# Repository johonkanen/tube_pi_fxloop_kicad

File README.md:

# Board renders

Rendered by CI from `johonkanen/tube_pi_fxloop_kicad` commit [`0b77b446ac`](https://github.com/johonkanen/tube_pi_fxloop_kicad/commit/0b77b446ac5b79dcb2dc1872e636383eb3f512de) on 2026-11-24 21:37 UTC with 10.0.7.
This branch is force-pushed on every render; do not commit to it.

## tube_pi_fxloop_revb (`rev_b/kicad/tube_pi_fxloop_revb.kicad_pcb`)

Copper layers:
- [B_Cu](tube_pi_fxloop_revb/B_Cu.png)
- [F_Cu](tube_pi_fxloop_revb/F_Cu.png)
- [In1_Cu](tube_pi_fxloop_revb/In1_Cu.png)
- [In2_Cu](tube_pi_fxloop_revb/In2_Cu.png)

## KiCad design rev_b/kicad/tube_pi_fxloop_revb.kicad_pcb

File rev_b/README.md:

# PI + FX loop rev B: schematic and layout (first pass)

The next PI + FX loop board of the 3-channel all-tube head, designed from the simulations and
documents of [tube_amplifier_kicad](https://github.com/johonkanen/tube_amplifier_kicad):
`sim/pi_nfb` (the reference for the PI and the feedback), `sim/fx_loop`, `docs/preamp_regulator.md`
and the interface contract `docs/interfaces.md` (**IF-1.2**: W23 per section 10.1 of 2026-11-22).
Second pass 2026-11-23: what changed and why, the interface check against IF-1.2 and the open items
are in [STATUS.md](STATUS.md), section "Second pass (2026-11-23)"; the third pass (same day,
the user's decisions: W24 Mini-Fit Jr, PI grid leaks to a fixed reference, 480 V raw, normalled
return) in section "Third pass (2026-11-23)". Rev A (the 2010 board,
converted) at the repo root is not touched; `rev_b/` is its own p2k board root
(`p2k_config.py`, PROJECT `tube_pi_fxloop_revb`), the same pattern as tube_preamp_kicad `rev_b/`.

Status and the interface check: [STATUS.md](STATUS.md). **Layout, first pass (2026-11-24):** STATUS.md
"Layout, first pass"; board `kicad/tube_pi_fxloop_revb.kicad_pcb`, renders `docs/layout_*.png`. The
interface sketch it was built on: STATUS.md "Layout sketch: interfaces", [docs/layout_sketch.png](docs/layout_sketch.png).

## Build

```
python3 rev_b/tools/make_lib.py          # lib/ from KiCad's stock symbol libraries (flattened)
python3 rev_b/tools/make_project.py      # project, root sheet, empty sub-sheets
python3 rev_b/tools/sheets/draw_all.py   # draws the five sheets; writes lib/footprint_map.csv and bom/bom.csv
python3 rev_b/tools/verify.py            # KiCad's netlist == the intended connections
rev_b/../tools/p2k/bin/kicad-cli sch erc rev_b/kicad/tube_pi_fxloop_revb.kicad_sch
```

The sheets are generated: edit `tools/sheets/draw_all.py`, not the `.kicad_sch` files, until the
draft is frozen. Drawing style is netlist-first (parts on a grid, a stub and a label on every pin),
exact for ERC and the netlist; a tidy layout pass comes later. **ERC: 0 errors, 0 warnings**
(KiCad 10). `verify.py`: 168 intended nets, 0 mismatches. **252 parts**: 140 R, 54 C, 21
transistors / JFETs, 9 diodes, 8 relays, 7 ICs, 11 connectors, 2 tubes.

**Footprints: all 252 assigned** (`lib/footprint_map.csv`, generated by `draw_all.py`, read by p2k's
sch_builder): KiCad 10 stock libraries except the three power-tab connectors J501-J503, which use
clearly marked local placeholders (`lib/tube_pi_fxloop_revb.pretty/PLACEHOLDER_Tab_x2_*`, two tabs
with 2 legs on 5.00 mm / 1.4 mm drill per interfaces.md 4.1; no stock Faston footprint exists).
Package rules: 0603 logic and gate drive, 0805 low-voltage audio, 1206 at HV nodes or > 0.1 W,
2512 for plate loads and every resistor string across HV (no SMD resistor over 200 V), C0G for
audio caps, THT film where an audio cap sees DC over 50 V, 105 °C electrolytics. The noval sockets
use `Valve:Valve_Noval_P` for now; rev A's `Valve_Noval_Belton_PCD21.00mm` matches the chassis holes
and goes in at layout. **BOM:** `bom/bom.csv`, 89 lines (qty, refs, value, footprint, candidate MPN,
LCSC, DNP, note); 37 lines carry the LCSC number the preamp rev B BOM checked on 2026-11-22 (same
part), the others an MPN or a specification. No stock check run.

| Sheet | Contents |
|---|---|
| 01 | J101 PRE IN (W22-b); 2.2M + 100n into the send cathode follower (V1 pins 1-3), whose grid is the >= 1 Mohm input buffer; SEND_SRC (1k) and the dry divider 47k / 4.7k; J102 FX ribbon (W23-a, IF-1.2: 2 SEND_SRC, 8 PAD_A, 10 PAD_B = GND, 16 RETURN_SIG); RETURN_SIG bleed 2.2M; return input 220n + 100k, the 0 / -20 dB pad (11k shunt switched by a JFET from the rear switch on PAD_A); series-shunt JFET mixer (100k branches, 220k); return stage (V1 pins 6-8, 680R unbypassed); 470n to the attenuator |
| 02 | PI-4 attenuator: five L-sections (1, 2, 4, 8, 16 dB, Z0 49.9k) on G6K-2F-Y relays, energised = section in (NO contacts; unpowered = 0 dB); PI: 10n input, 12AX7 LTP (V2), DN2540 CCS tail with a selected source resistor, equal 100k plates, 22n second-grid cap to the feedback node; J201 DRIVE (W24-a) with the soft-tied ground |
| 03 | J301 FB (W25-b), FB_RTN 0R to AGND (the OT secondary's one reference); per channel: relay at the 8 ohm end (both poles in parallel on the NO contacts), 1M bleed, Rf 100k + Cf 22p, Cres 22n, presence 1k and 22n, the 10-pin pot ribbon J302-J304 (W30-W32-b), NJFET T-switch (series, series, shunt) to the common node; Rbot 4.7k and a DNP step network on the common node |
| 04 | J401 CONTROL (W13-b, template); MCP23S17 (map of interfaces.md 7.2); 2x 74LVC1G11 (branch enable = FX_x AND FX_UNMUTE AND MUTE_ALL_N); 3x DG412 (10 of 12 switches: series gates pulled to -15 V and switched to GND, shunt gates pulled to GND and switched to -15 V); ULN2803A for the 8 relays; DGND island (GNDD) and its soft tie |
| 05 | J501 RAW HV (W03-b, no fuse in the feed); B+PI (3x 130 V, about 388 V) and B+FX (150 + 180 V, about 328 V) regulators, preamp_regulator.md rev B reference (STD4N80K5 DPAK, MMBTA42 on its pour = thermal foldback, HV strings in 2512: Rf 3x 330k, R3 3x 270k, bleed 3x 150k); RC decoupling (2.2k / 22u PI; 10k / 22u per FX triode); heater tabs J502 in (W07-b), J503 out (W08-a), floating; tube heaters |

## Layout (scripted; KiCad 10, KiCadRoutingTools in ~/dev/KiCadRoutingTools)

```
tools/p2k/bin/kipy rev_b/tools/make_pcb.py --force   # board from the netlist: outline / holes / sockets (rev A), connectors, rules
rev_b/layout/place.sh                                 # committed placement (placement_snapshot.json) + fix_place.py; ANNEAL=1 / SEEDS=1,2,.. re-anneals
rev_b/layout/route_chain.sh 0 13                      # heater, pours, 13 routing steps -> rev_b/layout/build/routed.kicad_pcb (about 25 min)
cp rev_b/layout/build/routed.kicad_pcb rev_b/kicad/tube_pi_fxloop_revb.kicad_pcb
tools/p2k/bin/kipy rev_b/layout/drc_exclusions.py      # the 4 explained exclusions (STATUS L3) into the .kicad_pro
rev_b/layout/drc.sh rev_b/kicad/tube_pi_fxloop_revb.kicad_pcb   # DRC + schematic parity with the project rules
tools/p2k/bin/kipy rev_b/layout/mech_check.py rev_b/kicad/tube_pi_fxloop_revb.kicad_pcb
tools/p2k/bin/kipy rev_b/layout/coupling_check.py rev_b/kicad/tube_pi_fxloop_revb.kicad_pcb
rev_b/layout/docs_renders.sh rev_b/kicad/tube_pi_fxloop_revb.kicad_pcb
```

`layout/placement.py` holds every mechanical figure (chassis frame, connector pin-1 positions,
pinned parts, pours); `layout/netclasses.py` the net classes and routing groups; `layout/make_groups.py`
the placement groups, zones and keep-outs; `layout/sketch_*.py` the interface sketch.

## Simulations (rev_b/sim, copies of the master repo's sim folders with the rev B changes)

- `sim/pi_nfb/run_open_load.py` → `results/open_load.md`: the PI loop margins with the rev B caps,
  the CCS tail and equal plates, with the speaker, an 8 ohm resistor, **no load** and a 100 ohm
  safety load. Result: loaded margins are as pi_nfb found (LF 56-61°, gain margin 15-17 dB), but
  **with no speaker the LF phase margin drops to 23-28° and the gain margin to about 8 dB** (the
  loop gain jumps to 26-28 dB at 1 kHz). 100n power coupling caps (220k grid leaks) give 37° /
  11.7 dB; a larger second-grid cap alone gives little (27° / 10 dB); a 100 ohm safety load little.
- Third pass: `sim/pi_burst/run_leak_ref.py` (PI grid-leak return, burst recovery),
  `sim/preamp_supply/run_raw480.py` (regulators at 430-480 V raw), `sim/fx_loop/run_normalled.py`
  (normalled return at 17 V peak); results in STATUS.md "Third pass".
- `sim/preamp_supply/run_thermal_foldback.py` → `results/thermal_foldback.md` (second pass; copied
  from the master repo, OUTPUTS set to this board's parts and loads, the bleed current counted in
  the pass device): at 70 °C ambient and 30-50 K/W, normal Q1 73-83 °C, limit 18-19 mA against
  2-3 mA loads, start-up and recovery fine; a steady short settles at 0.5-0.7 W, pass junction
  93-97 °C. No drain resistor needed (also with 8 mA loads).
- `sim/fx_loop/run_fx_revb.py` → `results/fx_revb.md` (re-run in the second pass with the 2.2M
  RETURN_SIG bleed: the return law moves by at most 0.1 dB): the FX loop re-derived for the 140 kohm
  preamp source and the rear pots / pad (IF-1.1): bypass gain preamp → PI input -3.8 dB (-3 dB at
  6 Hz and 21.5 kHz), input 1.5 Mohm at 1 kHz, send law, return law (log vs linear), headroom,
  noise (95 dB re nominal at every return-pot position), W23 send-to-return coupling (the leak is
  -43 dB at 1 kHz with 1 pF at mid pot settings: see STATUS.md), and the PI-4 attenuator steps
  (error ≤ 0.16 dB).

## Draft decisions (this board's own)

- **Input buffer = the send cathode follower.** Its bootstrapped grid gives 1.5 Mohm and a few pF;
  2.2M to GND defines the line. No pad in front of it, so the preamp sees no extra load.
- **Overall gain -3.8 dB** (preamp out → PI input, attenuator 0 dB): 20 V peak from the preamp
  reaches the PI at 13 V, under the 18 V limit of PI-4; 10 V nominal gives 6.4 V, +7 dB over the
  5 % onset at 400 V. Set by the dry divider (P = -22 dB) and the return stage's 680R unbypassed.
- **Series JFET gates: 100k / 10n, then 1M to the gate.** With the gate held at AC ground by the
  10n the gate junction conducts on the negative peaks (3 % THD at 9 V in); with the 1M the gate
  floats with the channel (1 % at 9 V, as fx_loop). Used in the mixer and the feedback T-switches.
- **Pad on a JFET, PAD_A as a DC line.** The rear switch grounds PAD_A (pulled to -15 V through 1M
  here, 100n at the connector); the JFET switches the 11k shunt. No audio node crosses the ribbon
  on PAD_A, and the rear I/O still sees a plain switch between PAD_A and PAD_B (GND).
- **PI-4 attenuator: relays** (decided here, interfaces.md 7.2 asks this board): the node carries
  up to 13 V peak (JFETs need under 2-8 V), JFETs after a fixed pad would cost the PI drive
  headroom, and latching relays would need 10 control lines (2 spare). Five G6K-2 relays,
  energised = section in, so 0 dB (full power) has all five off.
- **CCS: DN2540** (LND150's Idss can be under 2 mA), source resistor selected for 2.0 mA.
- **Regulator pass devices** (second pass, replaces the first pass's insulated TO-220F on the
  chassis): the rev B reference, STD4N80K5 DPAK on a copper pour with the current-limit MMBTA42 on
  the same pour (thermal foldback). The RAW_SS feed has no fuse (user, 2026-11-23); a steady short
  settles near 0.6 W (sim above), so no heatsink or chassis tie.
- **Relays:** Omron G6K-2F-Y 5 V (decided). The local symbol `G6K-2F-Y` (make_lib.py) is KiCad's
  G6K-2 with the contact arms redrawn to the datasheet (NC 4 / 5, NO 2 / 7); every function uses NO.

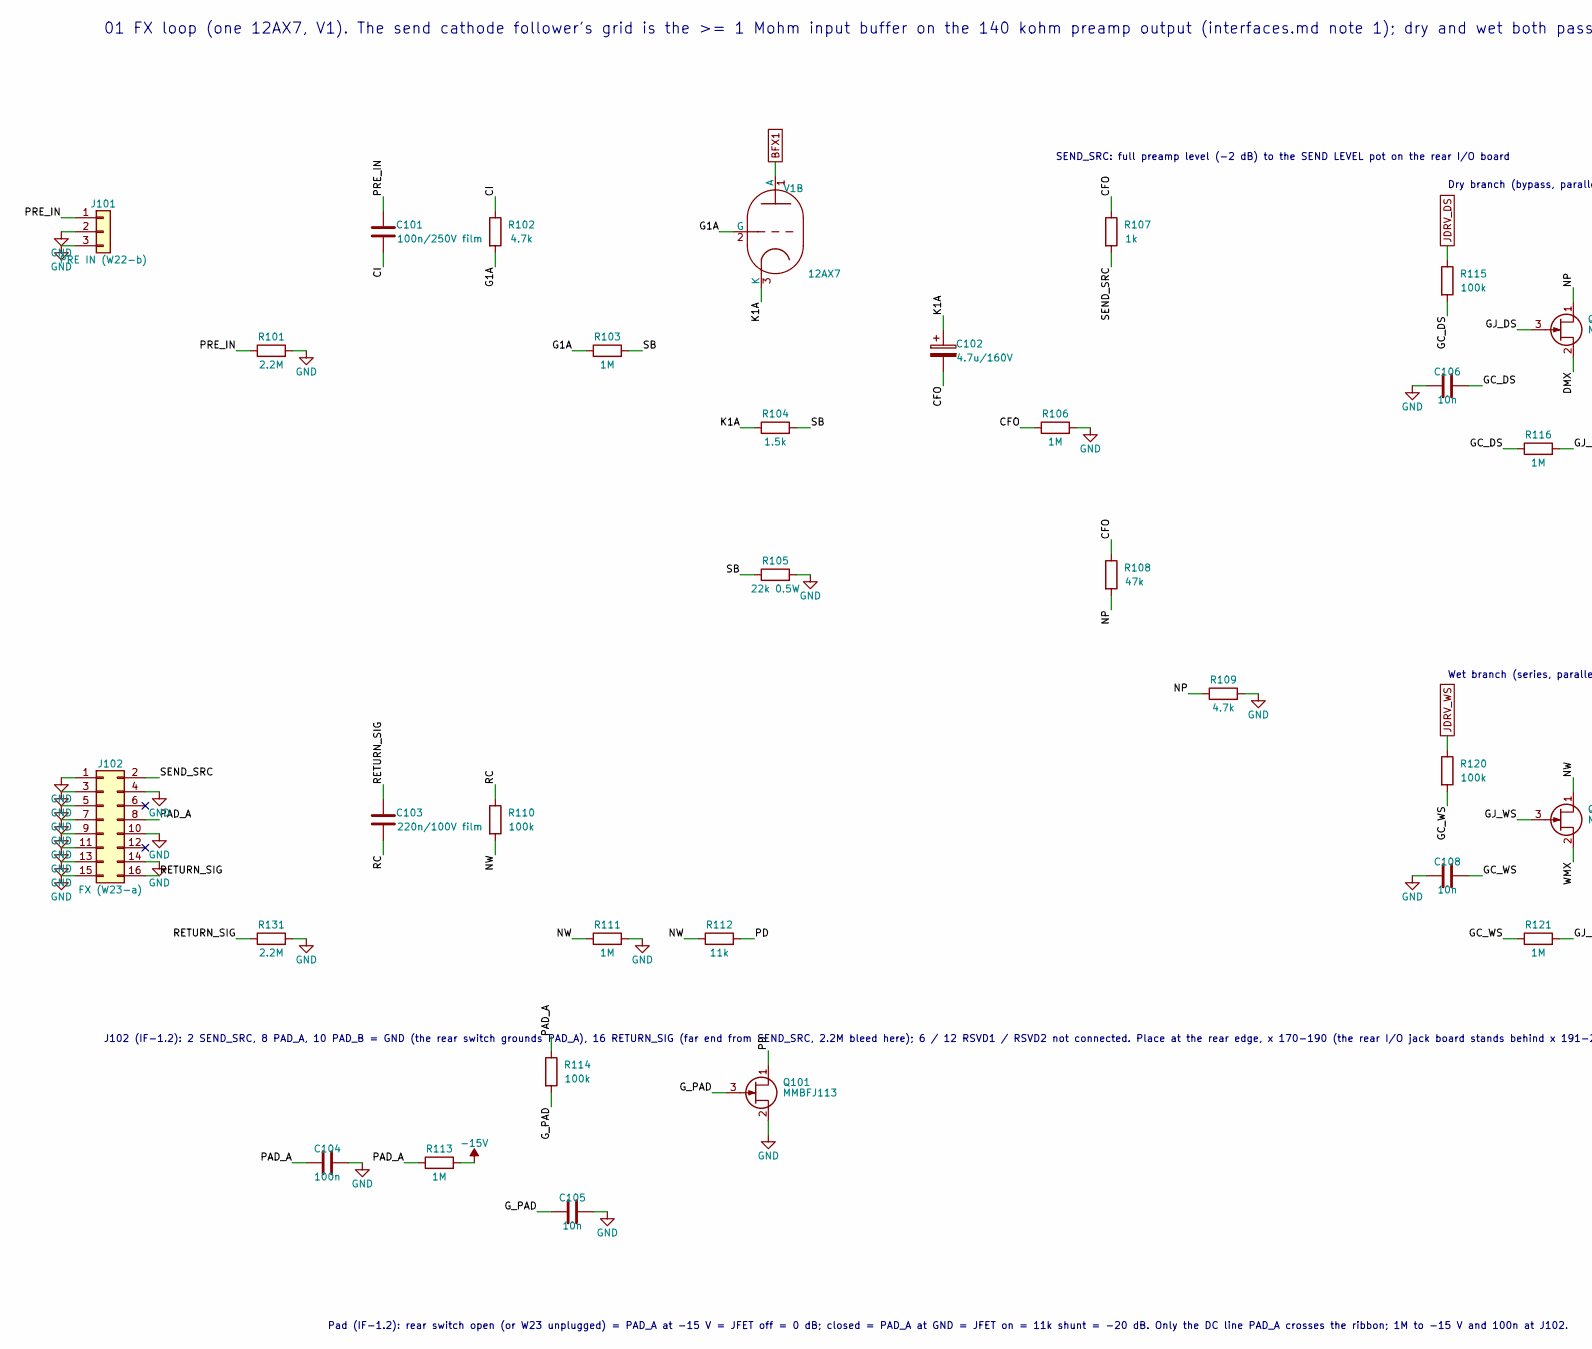
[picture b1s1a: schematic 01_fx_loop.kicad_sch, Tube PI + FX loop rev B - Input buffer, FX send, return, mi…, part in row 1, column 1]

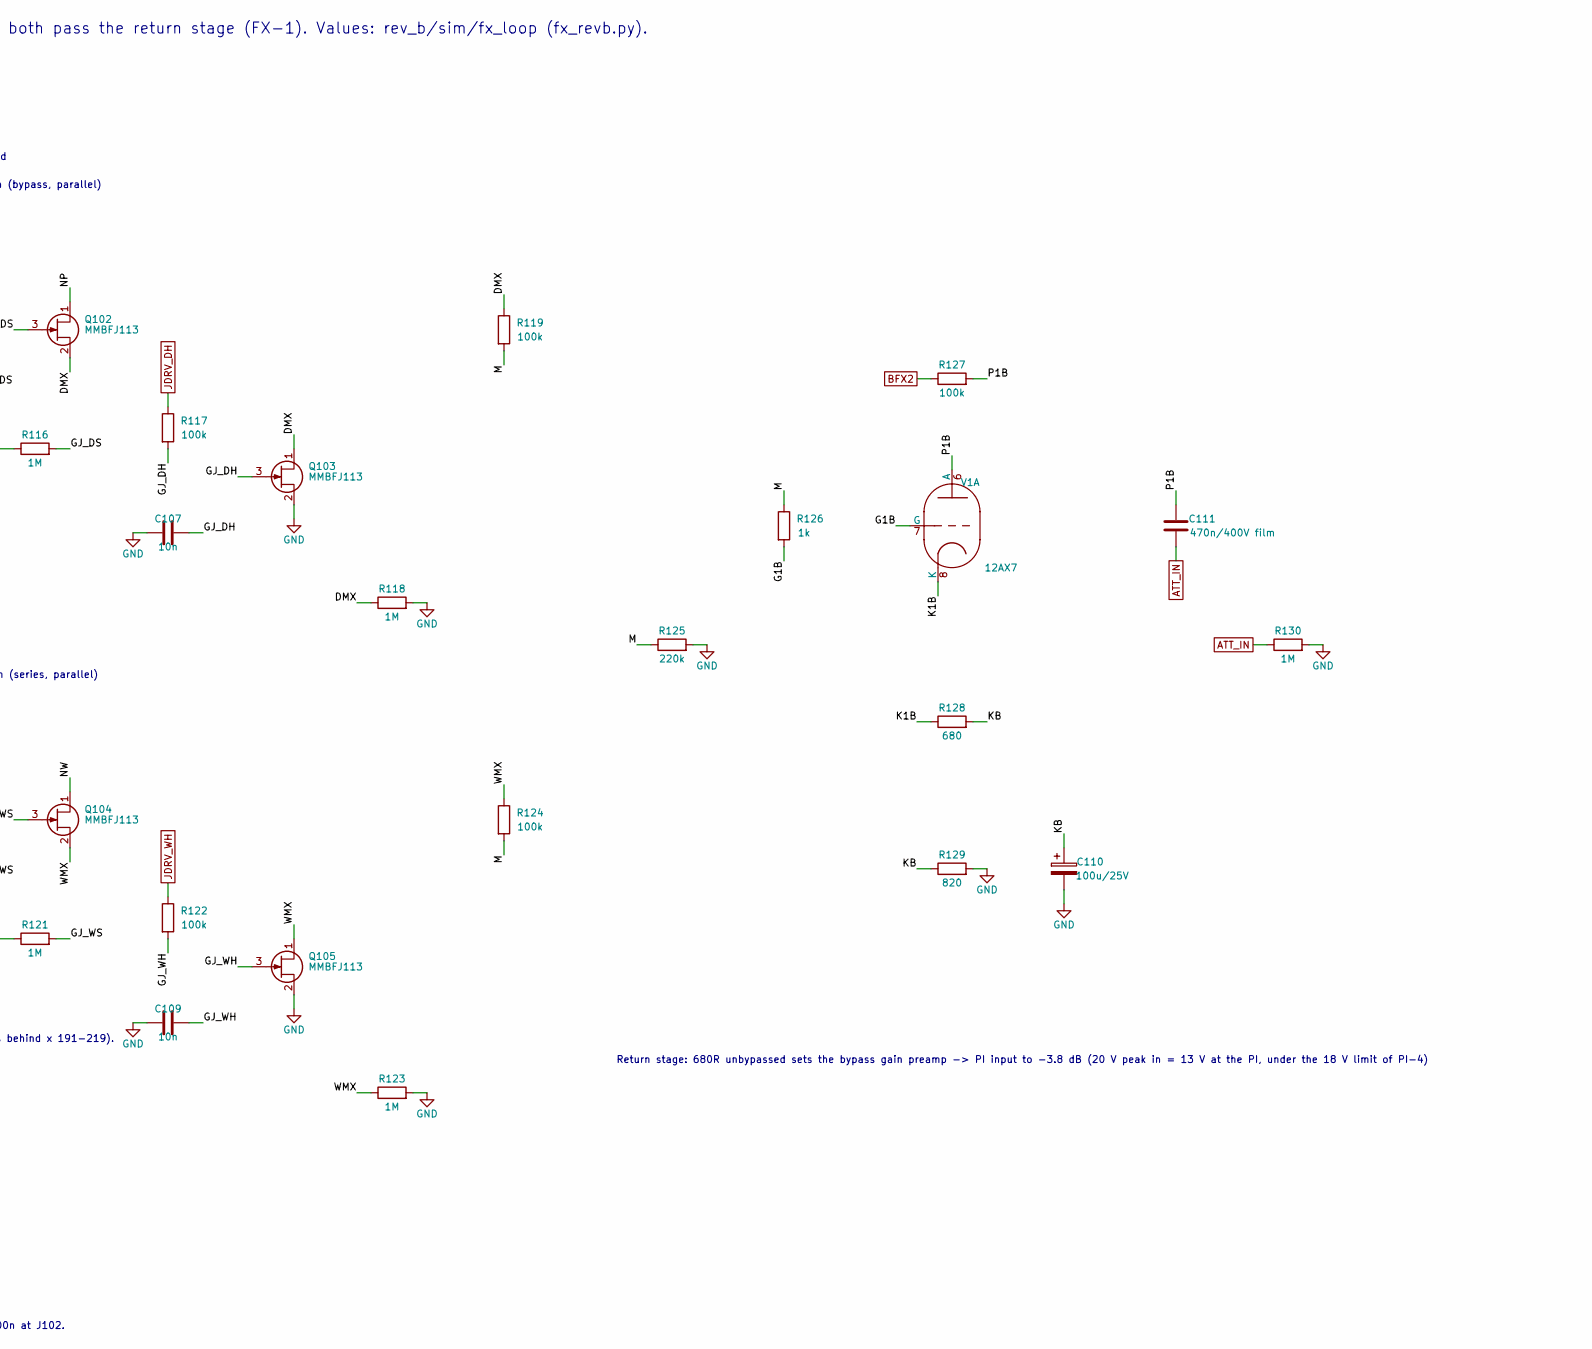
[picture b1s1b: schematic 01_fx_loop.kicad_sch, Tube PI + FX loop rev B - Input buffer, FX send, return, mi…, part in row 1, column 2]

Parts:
C101: 100n/250V film; C_Rect_L7.2mm_W4.5mm_P5.00mm_FKS2_FKP2_MKS2_MKP2
C102: 4.7u/160V; CP_Radial_D8.0mm_P3.50mm
C103: 220n/100V film; C_Rect_L7.2mm_W4.5mm_P5.00mm_FKS2_FKP2_MKS2_MKP2
C104: 100n; C_0603_1608Metric
C105, C106, C107, C108, C109: 10n; C_0603_1608Metric
C110: 100u/25V; CP_Elec_6.3x7.7
C111: 470n/400V film; C_Rect_L18.0mm_W8.0mm_P15.00mm_FKS3_FKP3
J101: PRE IN (W22-b); Molex_KK-254_AE-6410-03A_1x03_P2.54mm_Vertical
J102: FX (W23-a); IDC-Header_2x08_P2.54mm_Vertical
Q101, Q102, Q103, Q104, Q105: MMBFJ113; SOT-23
R101, R131: 2.2M; R_0805_2012Metric
R102, R109: 4.7k; R_0805_2012Metric
R103, R106, R111, R113, R118, R123, R130: 1M; R_0805_2012Metric
R104: 1.5k; R_0805_2012Metric
R105: 22k 0.5W; R_1206_3216Metric
R107, R126: 1k; R_0805_2012Metric
R108: 47k; R_0805_2012Metric
R110, R114, R119, R124: 100k; R_0805_2012Metric
R112: 11k; R_0805_2012Metric
R115, R117, R120, R122: 100k; R_0603_1608Metric
R116, R121: 1M; R_0603_1608Metric
R125: 220k; R_0805_2012Metric
R127: 100k; R_2512_6332Metric
R128: 680; R_0805_2012Metric
R129: 820; R_0805_2012Metric
V1: 12AX7; Valve_Noval_Belton_PCD21.00mm

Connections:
-15V: R113.2; also elsewhere on the board
/01 Input buffer, FX send, return, mixer, return stage/CFO: C102.2, R106.1, R107.1, R108.1
/01 Input buffer, FX send, return, mixer, return stage/CI: C101.2, R102.1
/01 Input buffer, FX send, return, mixer, return stage/DMX: Q102.2 (S), Q103.1 (D), R118.1, R119.1
/01 Input buffer, FX send, return, mixer, return stage/G1A: R102.2, R103.1, V1.2 (G)
/01 Input buffer, FX send, return, mixer, return stage/G1B: R126.2, V1.7 (G)
/01 Input buffer, FX send, return, mixer, return stage/GC_DS: C106.1, R115.2, R116.1
/01 Input buffer, FX send, return, mixer, return stage/GC_WS: C108.1, R120.2, R121.1
/01 Input buffer, FX send, return, mixer, return stage/GJ_DH: C107.1, Q103.3 (G), R117.2
/01 Input buffer, FX send, return, mixer, return stage/GJ_DS: Q102.3 (G), R116.2
/01 Input buffer, FX send, return, mixer, return stage/GJ_WH: C109.1, Q105.3 (G), R122.2
/01 Input buffer, FX send, return, mixer, return stage/GJ_WS: Q104.3 (G), R121.2
/01 Input buffer, FX send, return, mixer, return stage/G_PAD: C105.1, Q101.3 (G), R114.2
/01 Input buffer, FX send, return, mixer, return stage/K1A: C102.1, R104.1, V1.3 (K)
/01 Input buffer, FX send, return, mixer, return stage/K1B: R128.1, V1.8 (K)
/01 Input buffer, FX send, return, mixer, return stage/KB: C110.1, R128.2, R129.1
/01 Input buffer, FX send, return, mixer, return stage/M: R119.2, R124.2, R125.1, R126.1
/01 Input buffer, FX send, return, mixer, return stage/NP: Q102.1 (D), R108.2, R109.1
/01 Input buffer, FX send, return, mixer, return stage/NW: Q104.1 (D), R110.2, R111.1, R112.1
/01 Input buffer, FX send, return, mixer, return stage/P1B: C111.1, R127.2, V1.6 (A)
/01 Input buffer, FX send, return, mixer, return stage/PAD_A: C104.1, J102.8, R113.1, R114.1
/01 Input buffer, FX send, return, mixer, return stage/PD: Q101.1 (D), R112.2
/01 Input buffer, FX send, return, mixer, return stage/PRE_IN: C101.1, J101.1, R101.1
/01 Input buffer, FX send, return, mixer, return stage/RC: C103.2, R110.1
/01 Input buffer, FX send, return, mixer, return stage/RETURN_SIG: C103.1, J102.16, R131.1
/01 Input buffer, FX send, return, mixer, return stage/SB: R103.2, R104.2, R105.1
/01 Input buffer, FX send, return, mixer, return stage/SEND_SRC: J102.2, R107.2
/01 Input buffer, FX send, return, mixer, return stage/WMX: Q104.2 (S), Q105.1 (D), R123.1, R124.1
ATT_IN: C111.2, R130.1; also elsewhere on the board
BFX1: V1.1 (A); also elsewhere on the board
BFX2: R127.1; also elsewhere on the board
GND: C104.2, C105.2, C106.2, C107.2, C108.2, C109.2, C110.2, J101.2, J101.3, J102.1, J102.3, J102.4, J102.5, J102.7, J102.9, J102.10, J102.11, J102.13, J102.14, J102.15, Q101.2 (S), Q103.2 (S), Q105.2 (S), R101.2, R105.2, R106.2, R109.2, R111.2, R118.2, R123.2, R125.2, R129.2, R130.2, R131.2; also elsewhere on the board
JDRV_DH: R117.1; also elsewhere on the board
JDRV_DS: R115.1; also elsewhere on the board
JDRV_WH: R122.1; also elsewhere on the board
JDRV_WS: R120.1; also elsewhere on the board

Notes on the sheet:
01 FX loop (one 12AX7, V1). The send cathode follower's grid is the >= 1 Mohm input buffer on the 140 kohm preamp output (interfaces.md note 1); dry and wet both pass the return stage (FX-1). Values: rev_b/sim/fx_loop (fx_revb.py).
J102 (IF-1.2): 2 SEND_SRC, 8 PAD_A, 10 PAD_B = GND (the rear switch grounds PAD_A), 16 RETURN_SIG (far end from SEND_SRC, 2.2M bleed here); 6 / 12 RSVD1 / RSVD2 not connected. Place at the rear edge, x 170-190 (the rear I/O jack board stands behind x 191-219).
SEND_SRC: full preamp level (-2 dB) to the SEND LEVEL pot on the rear I/O board
Pad (IF-1.2): rear switch open (or W23 unplugged) = PAD_A at -15 V = JFET off = 0 dB; closed = PAD_A at GND = JFET on = 11k shunt = -20 dB. Only the DC line PAD_A crosses the ribbon; 1M to -15 V and 100n at J102.
Dry branch (bypass, parallel)
Wet branch (series, parallel)
Return stage: 680R unbypassed sets the bypass gain preamp -> PI input to -3.8 dB (20 V peak in = 13 V at the PI, under the 18 V limit of PI-4)

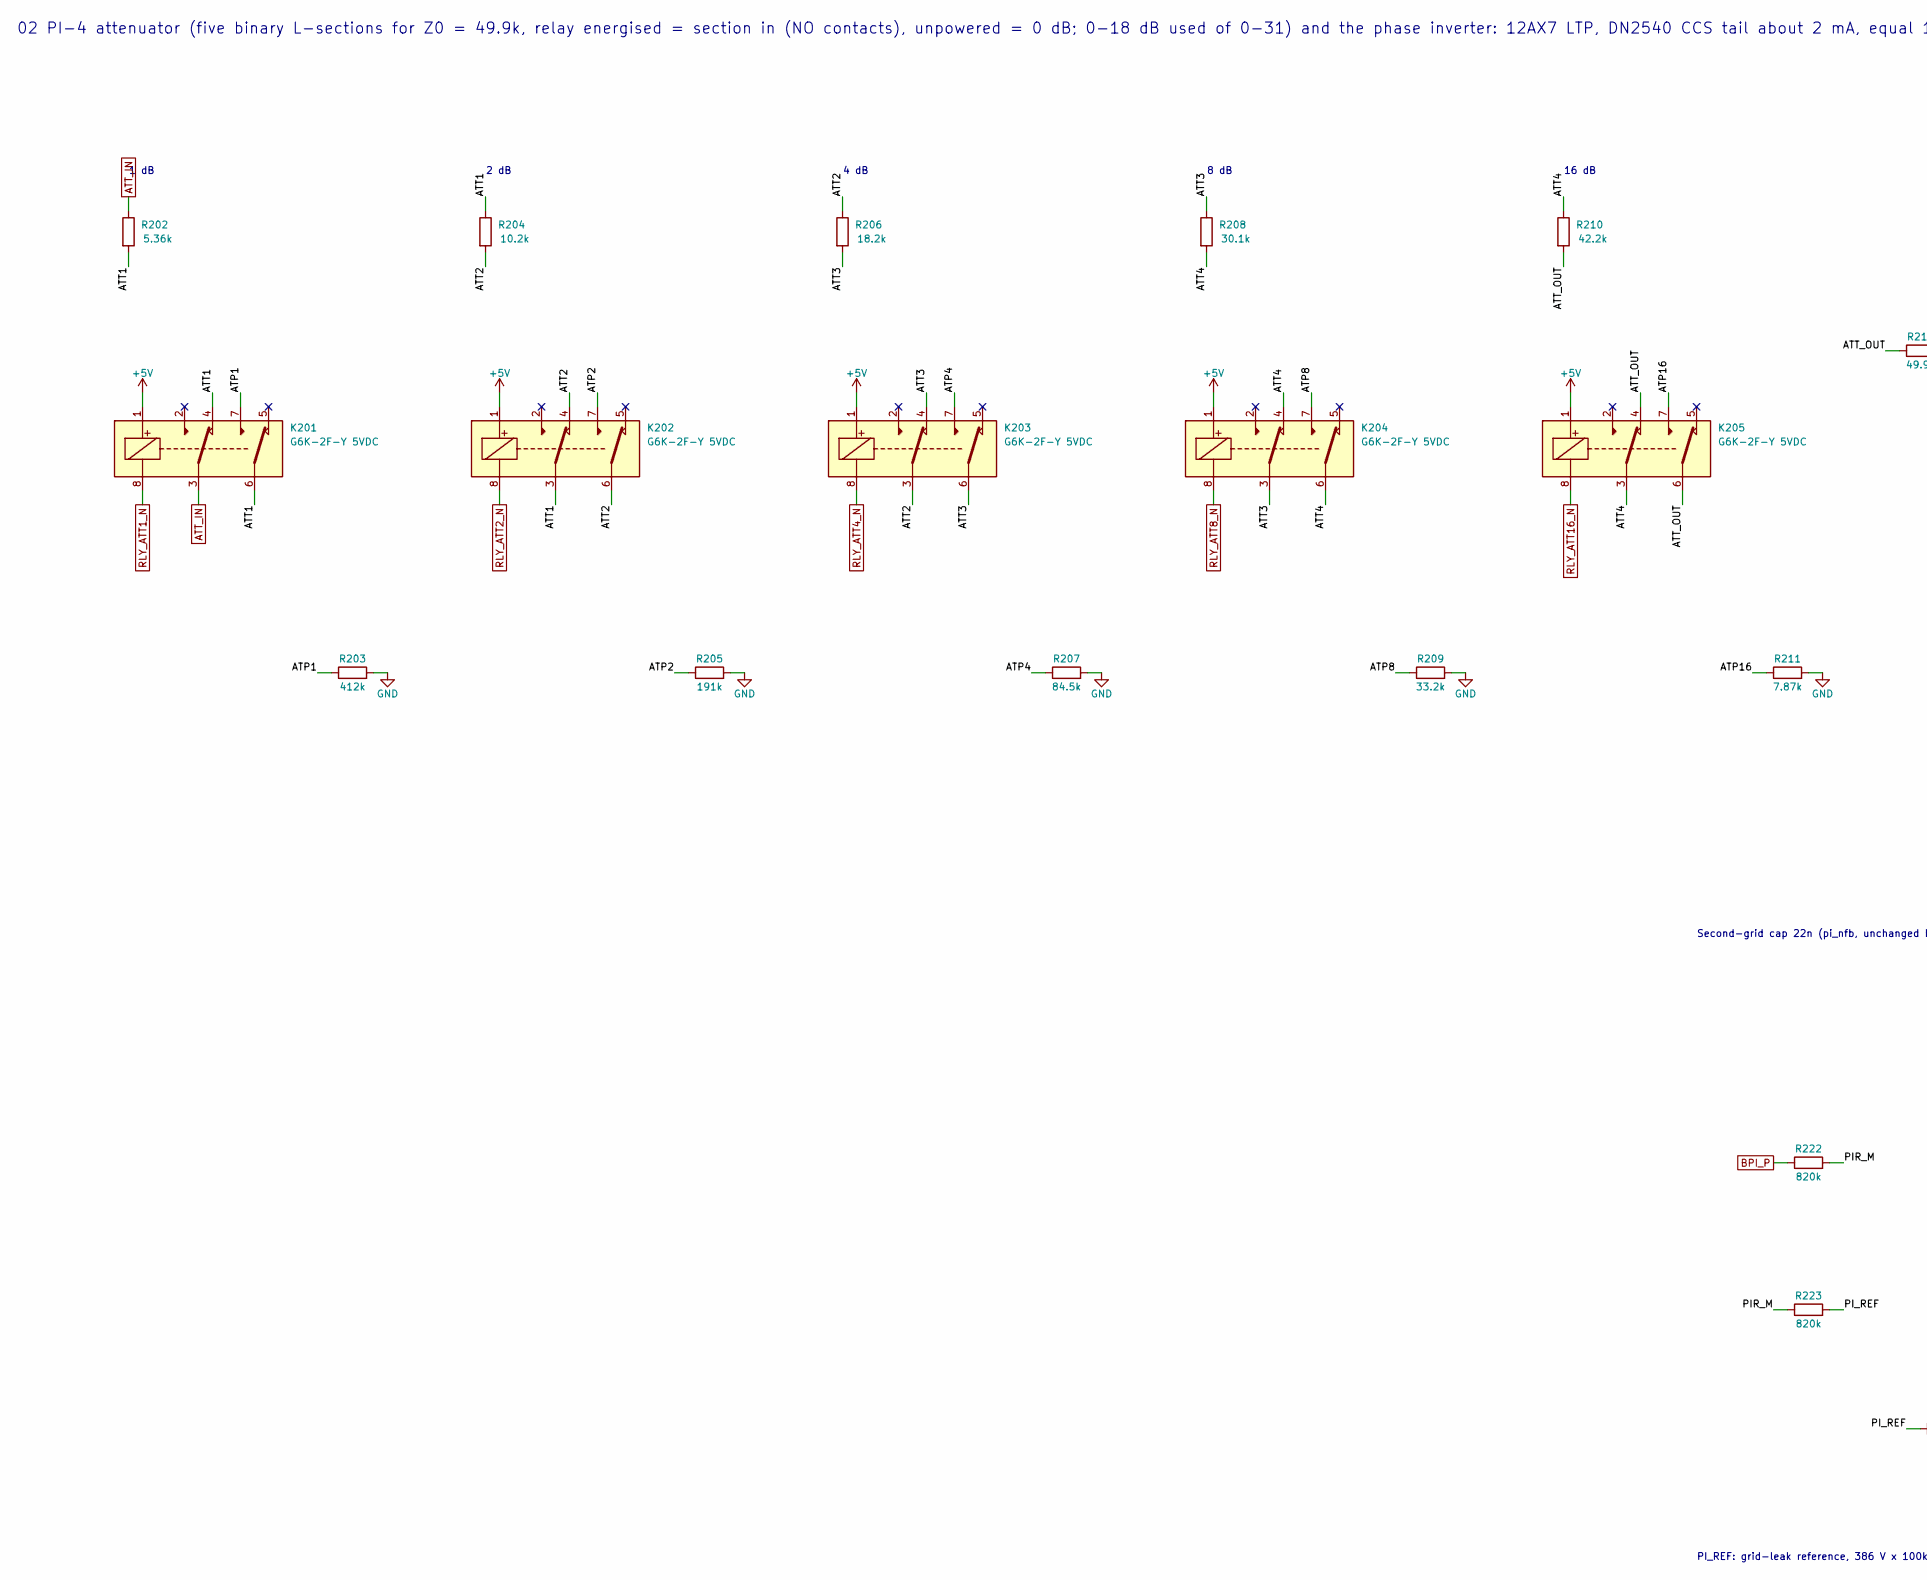
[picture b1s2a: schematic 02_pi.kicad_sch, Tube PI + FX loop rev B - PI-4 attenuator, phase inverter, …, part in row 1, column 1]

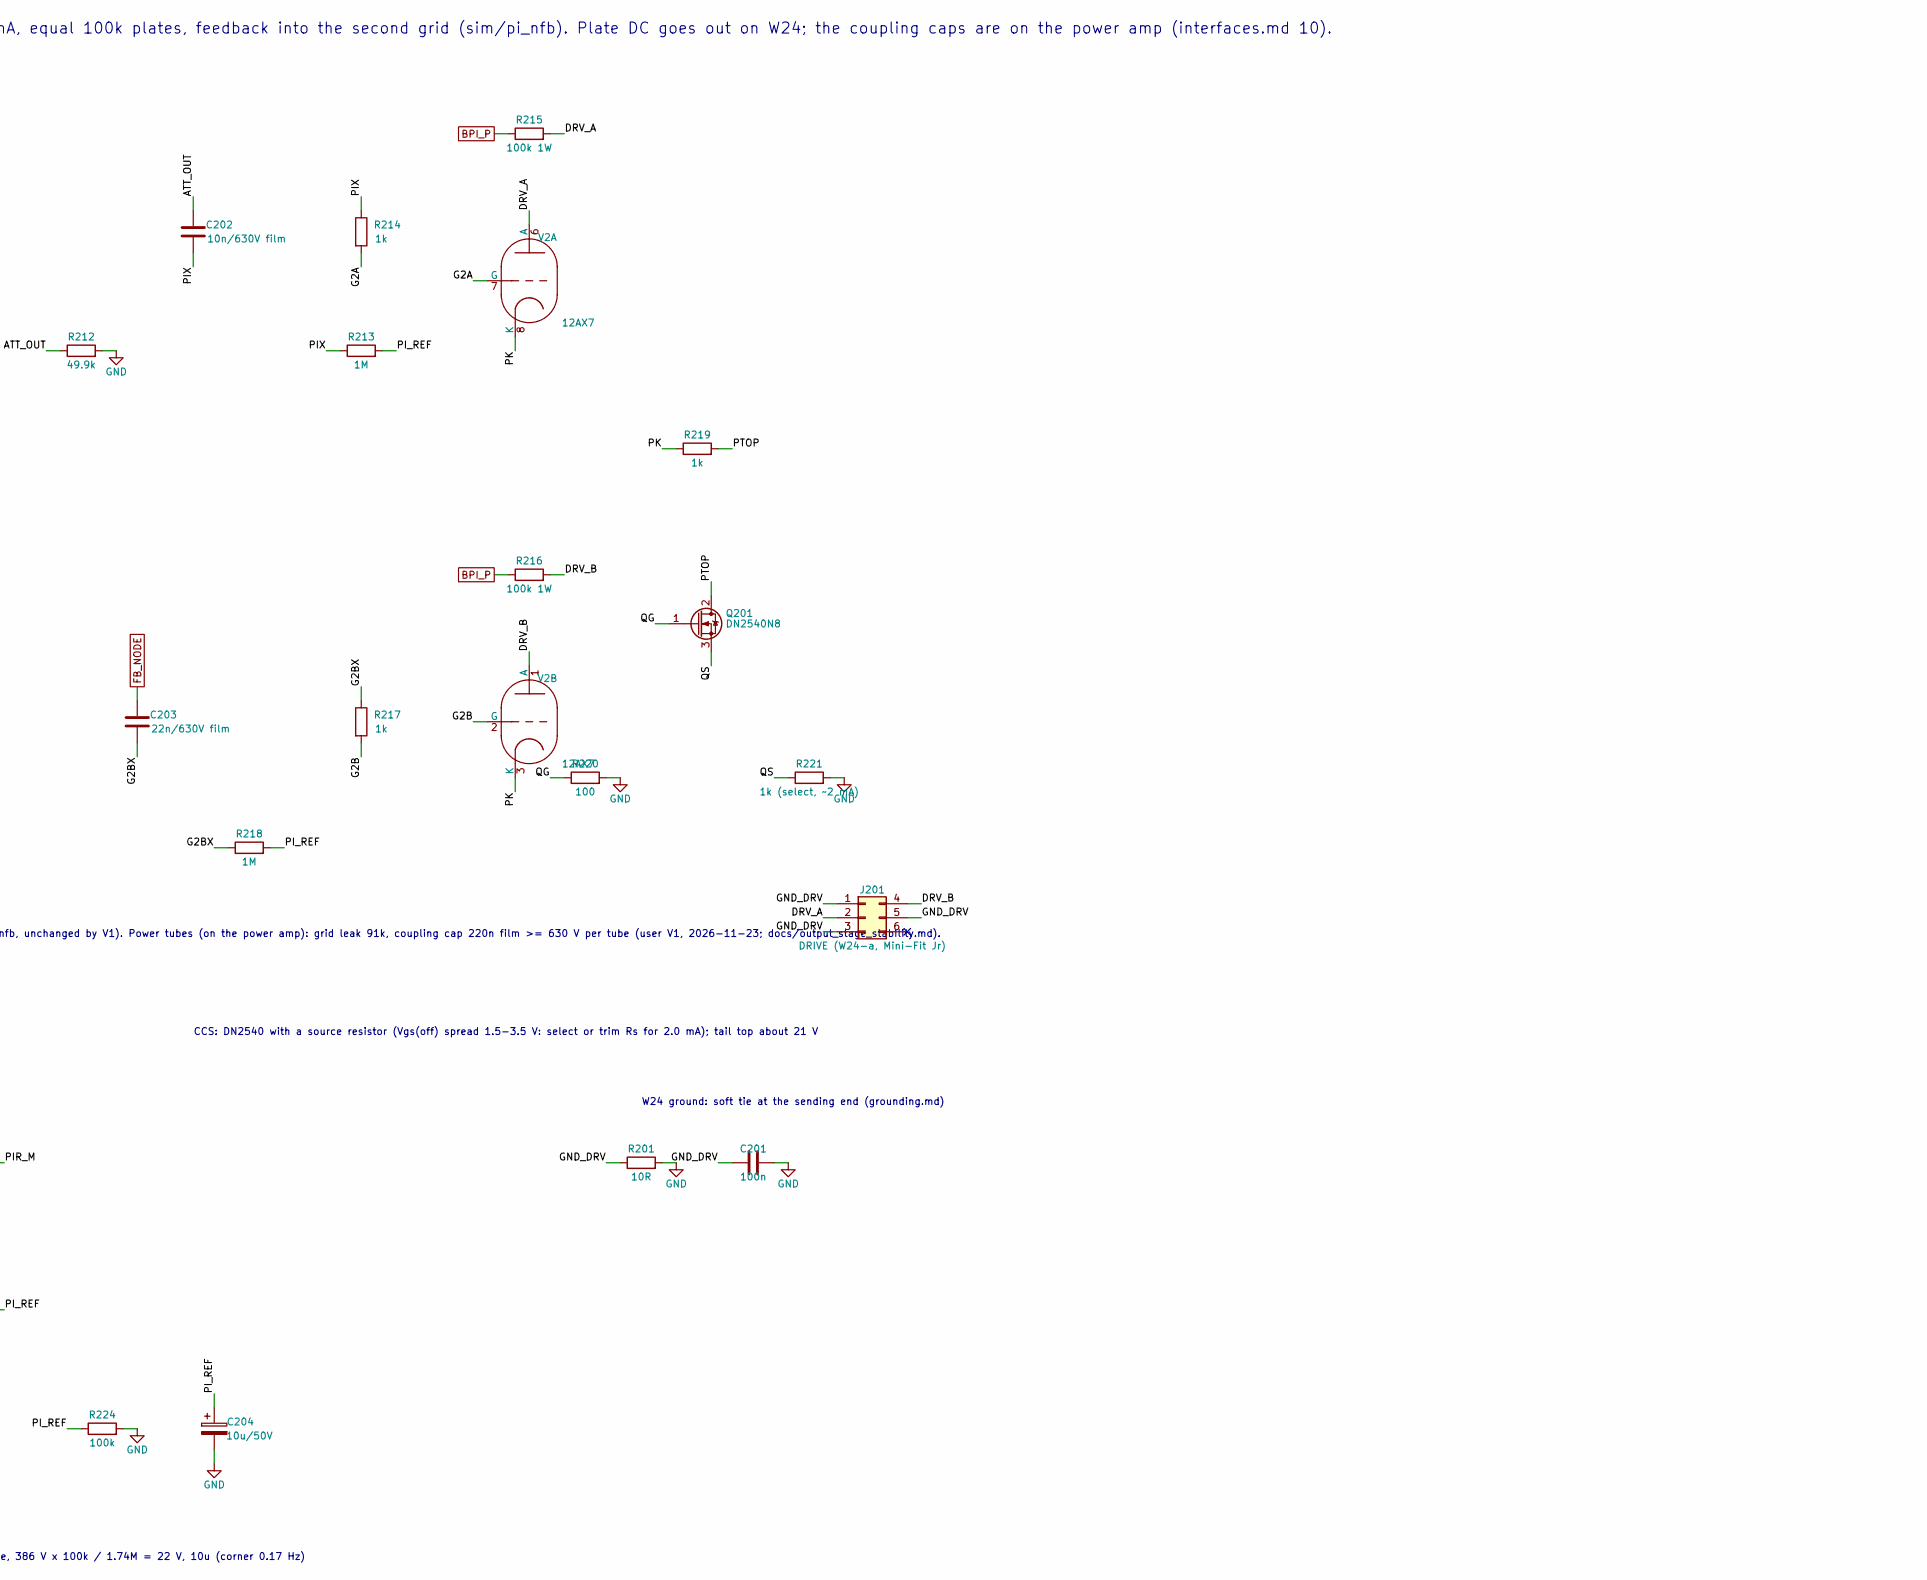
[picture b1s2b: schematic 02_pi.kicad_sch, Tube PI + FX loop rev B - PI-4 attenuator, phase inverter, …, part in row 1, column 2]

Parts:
C201: 100n; C_0603_1608Metric
C202: 10n/630V film; C_Rect_L13.0mm_W5.0mm_P10.00mm_FKS3_FKP3_MKS4
C203: 22n/630V film; C_Rect_L13.0mm_W5.0mm_P10.00mm_FKS3_FKP3_MKS4
C204: 10u/50V; CP_Elec_5x5.4
J201: DRIVE (W24-a, Mini-Fit Jr); Molex_Mini-Fit_Jr_5566-06A_2x03_P4.20mm_Vertical
K201, K202, K203, K204, K205: G6K-2F-Y 5VDC; Relay_DPDT_Omron_G6K-2F-Y
Q201: DN2540N8; SOT-89-3
R201: 10R; R_0603_1608Metric
R202: 5.36k; R_0805_2012Metric
R203: 412k; R_0805_2012Metric
R204: 10.2k; R_0805_2012Metric
R205: 191k; R_0805_2012Metric
R206: 18.2k; R_0805_2012Metric
R207: 84.5k; R_0805_2012Metric
R208: 30.1k; R_0805_2012Metric
R209: 33.2k; R_0805_2012Metric
R210: 42.2k; R_0805_2012Metric
R211: 7.87k; R_0805_2012Metric
R212: 49.9k; R_0805_2012Metric
R213, R218: 1M; R_0805_2012Metric
R214, R217, R219: 1k; R_0805_2012Metric
R215, R216: 100k 1W; R_2512_6332Metric
R220: 100; R_0805_2012Metric
R221: 1k (select, ~2 mA); R_0805_2012Metric
R222, R223: 820k; R_2512_6332Metric
R224: 100k; R_0805_2012Metric
V2: 12AX7; Valve_Noval_Belton_PCD21.00mm_Pin6_3.8mm

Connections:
+5V: K201.1, K202.1, K203.1, K204.1, K205.1; also elsewhere on the board
/02 PI-4 attenuator, phase inverter, grid drive/ATP1: K201.7, R203.1
/02 PI-4 attenuator, phase inverter, grid drive/ATP2: K202.7, R205.1
/02 PI-4 attenuator, phase inverter, grid drive/ATP4: K203.7, R207.1
/02 PI-4 attenuator, phase inverter, grid drive/ATP8: K204.7, R209.1
/02 PI-4 attenuator, phase inverter, grid drive/ATP16: K205.7, R211.1
/02 PI-4 attenuator, phase inverter, grid drive/ATT1: K201.4, K201.6, K202.3, R202.2, R204.1
/02 PI-4 attenuator, phase inverter, grid drive/ATT2: K202.4, K202.6, K203.3, R204.2, R206.1
/02 PI-4 attenuator, phase inverter, grid drive/ATT3: K203.4, K203.6, K204.3, R206.2, R208.1
/02 PI-4 attenuator, phase inverter, grid drive/ATT4: K204.4, K204.6, K205.3, R208.2, R210.1
/02 PI-4 attenuator, phase inverter, grid drive/ATT_OUT: C202.1, K205.4, K205.6, R210.2, R212.1
/02 PI-4 attenuator, phase inverter, grid drive/DRV_A: J201.2, R215.2, V2.6 (A)
/02 PI-4 attenuator, phase inverter, grid drive/DRV_B: J201.4, R216.2, V2.1 (A)
/02 PI-4 attenuator, phase inverter, grid drive/G2A: R214.2, V2.7 (G)
/02 PI-4 attenuator, phase inverter, grid drive/G2B: R217.2, V2.2 (G)
/02 PI-4 attenuator, phase inverter, grid drive/G2BX: C203.2, R217.1, R218.1
/02 PI-4 attenuator, phase inverter, grid drive/GND_DRV: C201.1, J201.1, J201.3, J201.5, R201.1
/02 PI-4 attenuator, phase inverter, grid drive/PIR_M: R222.2, R223.1
/02 PI-4 attenuator, phase inverter, grid drive/PIX: C202.2, R213.1, R214.1
/02 PI-4 attenuator, phase inverter, grid drive/PI_REF: C204.1, R213.2, R218.2, R223.2, R224.1
/02 PI-4 attenuator, phase inverter, grid drive/PK: R219.1, V2.3 (K), V2.8 (K)
/02 PI-4 attenuator, phase inverter, grid drive/PTOP: Q201.2 (D), R219.2
/02 PI-4 attenuator, phase inverter, grid drive/QG: Q201.1 (G), R220.1
/02 PI-4 attenuator, phase inverter, grid drive/QS: Q201.3 (S), R221.1
ATT_IN: K201.3, R202.1; also elsewhere on the board
BPI_P: R215.1, R216.1, R222.1; also elsewhere on the board
FB_NODE: C203.1; also elsewhere on the board
GND: C201.2, C204.2, R201.2, R203.2, R205.2, R207.2, R209.2, R211.2, R212.2, R220.2, R221.2, R224.2; also elsewhere on the board
RLY_ATT1_N: K201.8; also elsewhere on the board
RLY_ATT2_N: K202.8; also elsewhere on the board
RLY_ATT4_N: K203.8; also elsewhere on the board
RLY_ATT8_N: K204.8; also elsewhere on the board
RLY_ATT16_N: K205.8; also elsewhere on the board

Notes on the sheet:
02 PI-4 attenuator (five binary L-sections for Z0 = 49.9k, relay energised = section in (NO contacts), unpowered = 0 dB; 0-18 dB used of 0-31) and the phase inverter: 12AX7 LTP, DN2540 CCS tail about 2 mA, equal 100k plates, feedback into the second grid (sim/pi_nfb). Plate DC goes out on W24; the 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
W24 ground: soft tie at the sending end (grounding.md)
1 dB
2 dB
4 dB
8 dB
16 dB
Second-grid cap 22n (pi_nfb, unchanged by V1). Power tubes (on the power amp): grid leak 91k, coupling cap 220n film >= 630 V per tube (user V1, 2026-11-23; docs/output_stage_stability.md).
CCS: DN2540 with a source resistor (Vgs(off) spread 1.5-3.5 V: select or trim Rs for 2.0 mA); tail top about 21 V
PI_REF: grid-leak reference, 386 V x 100k / 1.74M = 22 V, 10u (corner 0.17 Hz)
